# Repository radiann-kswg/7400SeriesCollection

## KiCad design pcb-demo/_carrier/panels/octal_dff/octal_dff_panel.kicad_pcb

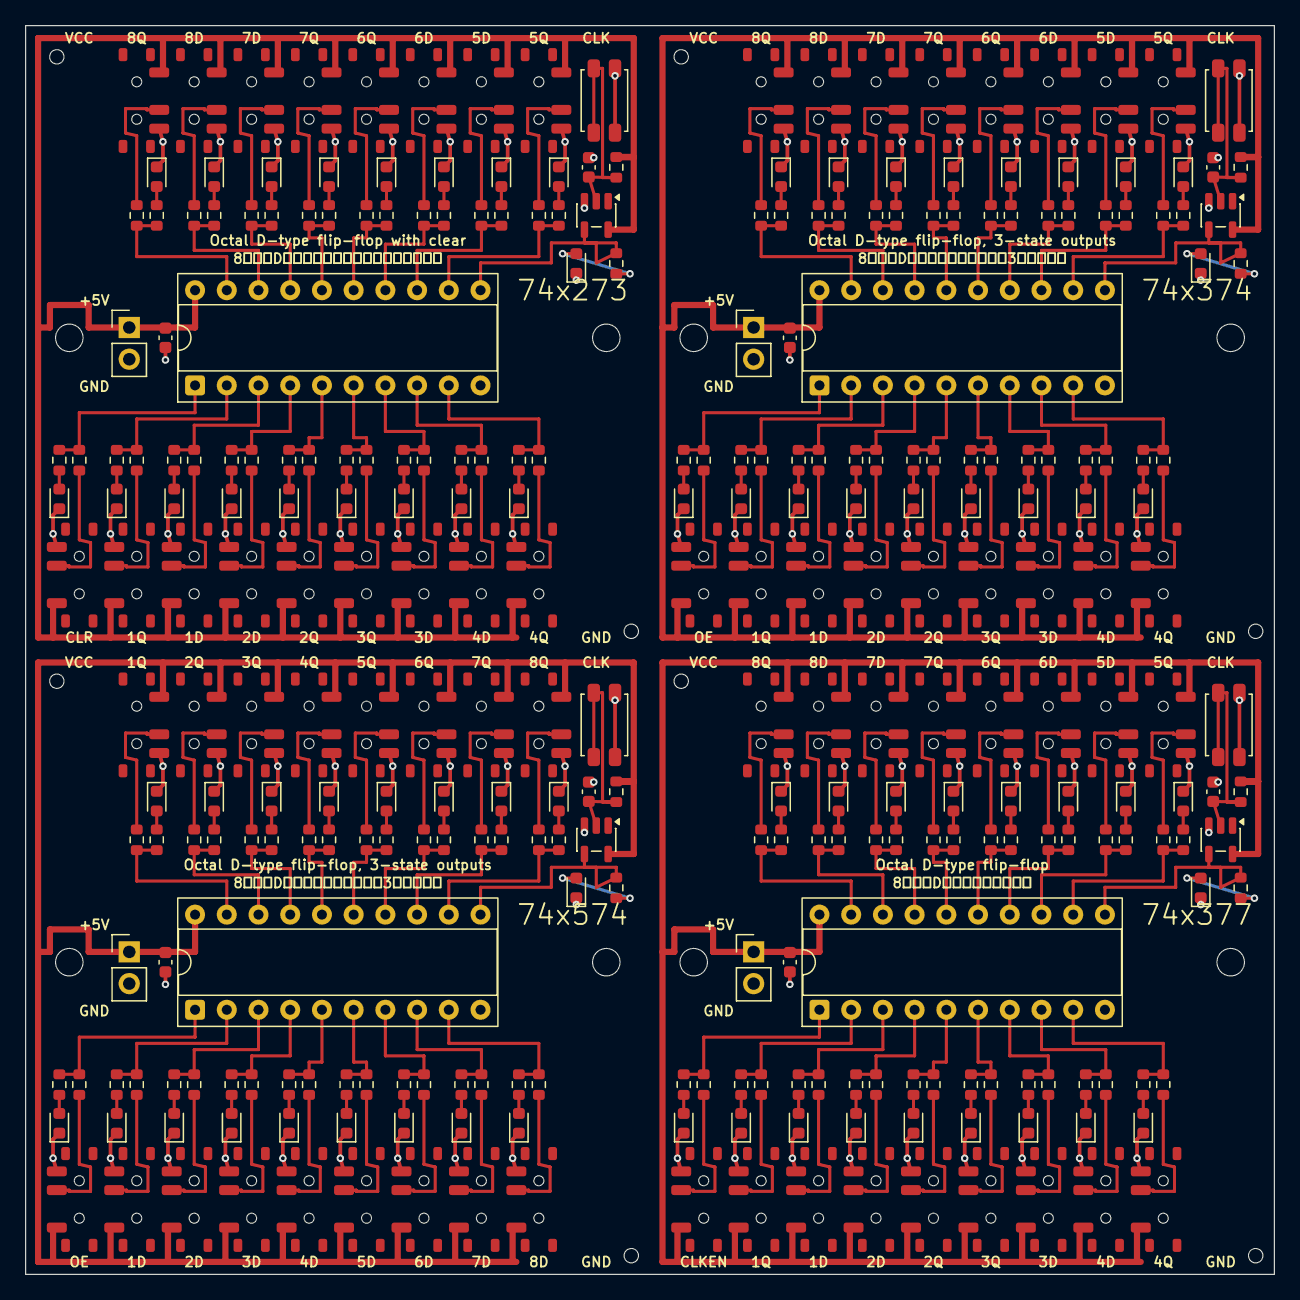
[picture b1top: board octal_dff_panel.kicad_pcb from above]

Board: 2 copper layers, 100.0 x 100.0 mm, 324 parts (0 on the bottom side), 224 nets.

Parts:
A_C1: 100nF; C_0603_1608Metric
A_CK11: 1uF; C_0603_1608Metric
A_D1, A_D3, A_D4, A_D7, A_D8, A_D11, A_D13, A_D14, A_D17, A_D18: RED; LED_0603_1608Metric
A_D2, A_D5, A_D6, A_D9, A_D12, A_D15, A_D16, A_D19: WHITE; LED_0603_1608Metric
A_J1: 5V_IN; PinHeader_1x02_P2.54mm_Vertical
A_MTG1, A_MTG2: MountingHole_2.2mm_M2
A_R1, A_R2, A_R3, A_R4, A_R5, A_R6, A_R7, A_R8, A_R9, A_R11, A_R12, A_R13, A_R14, A_R15, A_R16, A_R17, A_R18, A_R19: 4.7k; R_0603_1608Metric
A_R21, A_R22, A_R23, A_R24, A_R25, A_R26, A_R27, A_R28, A_R29, A_R32, A_R33, A_R34, A_R35, A_R36, A_R37, A_R38, A_R39: 220; R_0603_1608Metric
A_RC11: 10k; R_0603_1608Metric
A_SW1, A_SW2, A_SW3, A_SW4, A_SW5, A_SW6, A_SW7, A_SW8, A_SW9, A_SW12, A_SW13, A_SW14, A_SW15, A_SW16, A_SW17, A_SW18, A_SW19: MSS12C02LS-BB2.0; SW_SPDT_Shouhan_MSS12C02LS
A_SWT11: EVQP2R02M; SW_SPST_EVQP2_ShortPushTravel_H2.1mm
A_TH1, A_TH2: ToolingHole_1.152mm
A_U1: DIP20_Socket_300mil; DIP-20_W7.62mm_Socket
A_UG11: SN74LVC1G14DBVR; SOT-23-5
B_C1: 100nF; C_0603_1608Metric
B_CK11: 1uF; C_0603_1608Metric
B_D1, B_D3, B_D4, B_D7, B_D8, B_D11, B_D13, B_D14, B_D17, B_D18: RED; LED_0603_1608Metric
B_D2, B_D5, B_D6, B_D9, B_D12, B_D15, B_D16, B_D19: WHITE; LED_0603_1608Metric
B_J1: 5V_IN; PinHeader_1x02_P2.54mm_Vertical
B_MTG1, B_MTG2: MountingHole_2.2mm_M2
B_R1, B_R2, B_R3, B_R4, B_R5, B_R6, B_R7, B_R8, B_R9, B_R11, B_R12, B_R13, B_R14, B_R15, B_R16, B_R17, B_R18, B_R19: 4.7k; R_0603_1608Metric
B_R21, B_R22, B_R23, B_R24, B_R25, B_R26, B_R27, B_R28, B_R29, B_R32, B_R33, B_R34, B_R35, B_R36, B_R37, B_R38, B_R39: 220; R_0603_1608Metric
B_RC11: 10k; R_0603_1608Metric
B_SW1, B_SW2, B_SW3, B_SW4, B_SW5, B_SW6, B_SW7, B_SW8, B_SW9, B_SW12, B_SW13, B_SW14, B_SW15, B_SW16, B_SW17, B_SW18, B_SW19: MSS12C02LS-BB2.0; SW_SPDT_Shouhan_MSS12C02LS
B_SWT11: EVQP2R02M; SW_SPST_EVQP2_ShortPushTravel_H2.1mm
B_TH1, B_TH2: ToolingHole_1.152mm
B_U1: DIP20_Socket_300mil; DIP-20_W7.62mm_Socket
B_UG11: SN74LVC1G14DBVR; SOT-23-5
C_C1: 100nF; C_0603_1608Metric
C_CK11: 1uF; C_0603_1608Metric
C_D1, C_D2, C_D3, C_D4, C_D5, C_D6, C_D7, C_D8, C_D9, C_D11: RED; LED_0603_1608Metric
C_D12, C_D13, C_D14, C_D15, C_D16, C_D17, C_D18, C_D19: WHITE; LED_0603_1608Metric
C_J1: 5V_IN; PinHeader_1x02_P2.54mm_Vertical
C_MTG1, C_MTG2: MountingHole_2.2mm_M2
C_R1, C_R2, C_R3, C_R4, C_R5, C_R6, C_R7, C_R8, C_R9, C_R11, C_R12, C_R13, C_R14, C_R15, C_R16, C_R17, C_R18, C_R19: 4.7k; R_0603_1608Metric
C_R21, C_R22, C_R23, C_R24, C_R25, C_R26, C_R27, C_R28, C_R29, C_R32, C_R33, C_R34, C_R35, C_R36, C_R37, C_R38, C_R39: 220; R_0603_1608Metric
C_RC11: 10k; R_0603_1608Metric
C_SW1, C_SW2, C_SW3, C_SW4, C_SW5, C_SW6, C_SW7, C_SW8, C_SW9, C_SW12, C_SW13, C_SW14, C_SW15, C_SW16, C_SW17, C_SW18, C_SW19: MSS12C02LS-BB2.0; SW_SPDT_Shouhan_MSS12C02LS
C_SWT11: EVQP2R02M; SW_SPST_EVQP2_ShortPushTravel_H2.1mm
C_TH1, C_TH2: ToolingHole_1.152mm
C_U1: DIP20_Socket_300mil; DIP-20_W7.62mm_Socket
C_UG11: SN74LVC1G14DBVR; SOT-23-5
D_C1: 100nF; C_0603_1608Metric
D_CK11: 1uF; C_0603_1608Metric
D_D1, D_D3, D_D4, D_D7, D_D8, D_D11, D_D13, D_D14, D_D17, D_D18: RED; LED_0603_1608Metric
D_D2, D_D5, D_D6, D_D9, D_D12, D_D15, D_D16, D_D19: WHITE; LED_0603_1608Metric
D_J1: 5V_IN; PinHeader_1x02_P2.54mm_Vertical
D_MTG1, D_MTG2: MountingHole_2.2mm_M2
D_R1, D_R2, D_R3, D_R4, D_R5, D_R6, D_R7, D_R8, D_R9, D_R11, D_R12, D_R13, D_R14, D_R15, D_R16, D_R17, D_R18, D_R19: 4.7k; R_0603_1608Metric
D_R21, D_R22, D_R23, D_R24, D_R25, D_R26, D_R27, D_R28, D_R29, D_R32, D_R33, D_R34, D_R35, D_R36, D_R37, D_R38, D_R39: 220; R_0603_1608Metric
D_RC11: 10k; R_0603_1608Metric
D_SW1, D_SW2, D_SW3, D_SW4, D_SW5, D_SW6, D_SW7, D_SW8, D_SW9, D_SW12, D_SW13, D_SW14, D_SW15, D_SW16, D_SW17, D_SW18, D_SW19: MSS12C02LS-BB2.0; SW_SPDT_Shouhan_MSS12C02LS
D_SWT11: EVQP2R02M; SW_SPST_EVQP2_ShortPushTravel_H2.1mm
D_TH1, D_TH2: ToolingHole_1.152mm
D_U1: DIP20_Socket_300mil; DIP-20_W7.62mm_Socket
D_UG11: SN74LVC1G14DBVR; SOT-23-5

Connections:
A_+5V: A_C1.1, A_J1.1, A_RC11.1, A_SW1.1, A_SW2.1, A_SW3.1, A_SW4.1, A_SW5.1, A_SW6.1, A_SW7.1, A_SW8.1, A_SW9.1, A_SW12.1, A_SW13.1, A_SW14.1, A_SW15.1, A_SW16.1, A_SW17.1, A_SW18.1, A_SW19.1, A_U1.20, A_UG11.5
A_/CLKR11: A_CK11.1, A_RC11.2, A_SWT11.2, A_UG11.2
A_/LA1: A_D1.2, A_R1.1
A_/LA2: A_D2.2, A_R2.1
A_/LA3: A_D3.2, A_R3.1
A_/LA4: A_D4.2, A_R4.1
A_/LA5: A_D5.2, A_R5.1
A_/LA6: A_D6.2, A_R6.1
A_/LA7: A_D7.2, A_R7.1
A_/LA8: A_D8.2, A_R8.1
A_/LA9: A_D9.2, A_R9.1
A_/LA11: A_D11.2, A_R11.2
A_/LA12: A_D12.2, A_R12.1
A_/LA13: A_D13.2, A_R13.1
A_/LA14: A_D14.2, A_R14.1
A_/LA15: A_D15.2, A_R15.1
A_/LA16: A_D16.2, A_R16.1
A_/LA17: A_D17.2, A_R17.1
A_/LA18: A_D18.2, A_R18.1
A_/LA19: A_D19.2, A_R19.1
A_/P1: A_R1.2, A_R21.2, A_U1.1
A_/P2: A_R2.2, A_R22.2, A_U1.2
A_/P3: A_R3.2, A_R23.2, A_U1.3
A_/P4: A_R4.2, A_R24.2, A_U1.4
A_/P5: A_R5.2, A_R25.2, A_U1.5
A_/P6: A_R6.2, A_R26.2, A_U1.6
A_/P7: A_R7.2, A_R27.2, A_U1.7
A_/P8: A_R8.2, A_R28.2, A_U1.8
A_/P9: A_R9.2, A_R29.2, A_U1.9
A_/P11: A_R11.1, A_U1.11, A_UG11.4
A_/P12: A_R12.2, A_R32.2, A_U1.12
A_/P13: A_R13.2, A_R33.2, A_U1.13
A_/P14: A_R14.2, A_R34.2, A_U1.14
A_/P15: A_R15.2, A_R35.2, A_U1.15
A_/P16: A_R16.2, A_R36.2, A_U1.16
A_/P17: A_R17.2, A_R37.2, A_U1.17
A_/P18: A_R18.2, A_R38.2, A_U1.18
A_/P19: A_R19.2, A_R39.2, A_U1.19
A_/SWC1: A_R21.1, A_SW1.2
A_/SWC2: A_R22.1, A_SW2.2
A_/SWC3: A_R23.1, A_SW3.2
A_/SWC4: A_R24.1, A_SW4.2
A_/SWC5: A_R25.1, A_SW5.2
A_/SWC6: A_R26.1, A_SW6.2
A_/SWC7: A_R27.1, A_SW7.2
A_/SWC8: A_R28.1, A_SW8.2
A_/SWC9: A_R29.1, A_SW9.2
A_/SWC12: A_R32.1, A_SW12.2
A_/SWC13: A_R33.1, A_SW13.2
A_/SWC14: A_R34.1, A_SW14.2
A_/SWC15: A_R35.1, A_SW15.2
A_/SWC16: A_R36.1, A_SW16.2
A_/SWC17: A_R37.1, A_SW17.2
A_/SWC18: A_R38.1, A_SW18.2
A_/SWC19: A_R39.1, A_SW19.2
A_GND: A_C1.2, A_CK11.2, A_D1.1, A_D2.1, A_D3.1, A_D4.1, A_D5.1, A_D6.1, A_D7.1, A_D8.1, A_D9.1, A_D11.1, A_D12.1, A_D13.1, A_D14.1, A_D15.1, A_D16.1, A_D17.1, A_D18.1, A_D19.1, A_J1.2, A_SW1.3, A_SW2.3, A_SW3.3, A_SW4.3, A_SW5.3, A_SW6.3, A_SW7.3, A_SW8.3, A_SW9.3, A_SW12.3, A_SW13.3, A_SW14.3, A_SW15.3, A_SW16.3, A_SW17.3, A_SW18.3, A_SW19.3, A_SWT11.1, A_U1.10, A_UG11.3
B_+5V: B_C1.1, B_J1.1, B_RC11.1, B_SW1.1, B_SW2.1, B_SW3.1, B_SW4.1, B_SW5.1, B_SW6.1, B_SW7.1, B_SW8.1, B_SW9.1, B_SW12.1, B_SW13.1, B_SW14.1, B_SW15.1, B_SW16.1, B_SW17.1, B_SW18.1, B_SW19.1, B_U1.20, B_UG11.5
B_/CLKR11: B_CK11.1, B_RC11.2, B_SWT11.2, B_UG11.2
B_/LA1: B_D1.2, B_R1.1
B_/LA2: B_D2.2, B_R2.1
B_/LA3: B_D3.2, B_R3.1
B_/LA4: B_D4.2, B_R4.1
B_/LA5: B_D5.2, B_R5.1
B_/LA6: B_D6.2, B_R6.1
B_/LA7: B_D7.2, B_R7.1
B_/LA8: B_D8.2, B_R8.1
B_/LA9: B_D9.2, B_R9.1
B_/LA11: B_D11.2, B_R11.2
B_/LA12: B_D12.2, B_R12.1
B_/LA13: B_D13.2, B_R13.1
B_/LA14: B_D14.2, B_R14.1
B_/LA15: B_D15.2, B_R15.1
B_/LA16: B_D16.2, B_R16.1
B_/LA17: B_D17.2, B_R17.1
B_/LA18: B_D18.2, B_R18.1
B_/LA19: B_D19.2, B_R19.1
B_/P1: B_R1.2, B_R21.2, B_U1.1
B_/P2: B_R2.2, B_R22.2, B_U1.2
B_/P3: B_R3.2, B_R23.2, B_U1.3
B_/P4: B_R4.2, B_R24.2, B_U1.4
B_/P5: B_R5.2, B_R25.2, B_U1.5
B_/P6: B_R6.2, B_R26.2, B_U1.6
B_/P7: B_R7.2, B_R27.2, B_U1.7
B_/P8: B_R8.2, B_R28.2, B_U1.8
B_/P9: B_R9.2, B_R29.2, B_U1.9
B_/P11: B_R11.1, B_U1.11, B_UG11.4
B_/P12: B_R12.2, B_R32.2, B_U1.12
B_/P13: B_R13.2, B_R33.2, B_U1.13
B_/P14: B_R14.2, B_R34.2, B_U1.14
B_/P15: B_R15.2, B_R35.2, B_U1.15
B_/P16: B_R16.2, B_R36.2, B_U1.16
B_/P17: B_R17.2, B_R37.2, B_U1.17
B_/P18: B_R18.2, B_R38.2, B_U1.18
B_/P19: B_R19.2, B_R39.2, B_U1.19
B_/SWC1: B_R21.1, B_SW1.2
B_/SWC2: B_R22.1, B_SW2.2
B_/SWC3: B_R23.1, B_SW3.2
B_/SWC4: B_R24.1, B_SW4.2
B_/SWC5: B_R25.1, B_SW5.2
B_/SWC6: B_R26.1, B_SW6.2
B_/SWC7: B_R27.1, B_SW7.2
B_/SWC8: B_R28.1, B_SW8.2
B_/SWC9: B_R29.1, B_SW9.2
B_/SWC12: B_R32.1, B_SW12.2
B_/SWC13: B_R33.1, B_SW13.2
B_/SWC14: B_R34.1, B_SW14.2
B_/SWC15: B_R35.1, B_SW15.2
B_/SWC16: B_R36.1, B_SW16.2
B_/SWC17: B_R37.1, B_SW17.2
B_/SWC18: B_R38.1, B_SW18.2
B_/SWC19: B_R39.1, B_SW19.2
B_GND: B_C1.2, B_CK11.2, B_D1.1, B_D2.1, B_D3.1, B_D4.1, B_D5.1, B_D6.1, B_D7.1, B_D8.1, B_D9.1, B_D11.1, B_D12.1, B_D13.1, B_D14.1, B_D15.1, B_D16.1, B_D17.1, B_D18.1, B_D19.1, B_J1.2, B_SW1.3, B_SW2.3, B_SW3.3, B_SW4.3, B_SW5.3, B_SW6.3, B_SW7.3, B_SW8.3, B_SW9.3, B_SW12.3, B_SW13.3, B_SW14.3, B_SW15.3, B_SW16.3, B_SW17.3, B_SW18.3, B_SW19.3, B_SWT11.1, B_U1.10, B_UG11.3
C_+5V: C_C1.1, C_J1.1, C_RC11.1, C_SW1.1, C_SW2.1, C_SW3.1, C_SW4.1, C_SW5.1, C_SW6.1, C_SW7.1, C_SW8.1, C_SW9.1, C_SW12.1, C_SW13.1, C_SW14.1, C_SW15.1, C_SW16.1, C_SW17.1, C_SW18.1, C_SW19.1, C_U1.20, C_UG11.5
C_/CLKR11: C_CK11.1, C_RC11.2, C_SWT11.2, C_UG11.2
C_/LA1: C_D1.2, C_R1.1
C_/LA2: C_D2.2, C_R2.1
C_/LA3: C_D3.2, C_R3.1
C_/LA4: C_D4.2, C_R4.1
C_/LA5: C_D5.2, C_R5.1
C_/LA6: C_D6.2, C_R6.1
C_/LA7: C_D7.2, C_R7.1
C_/LA8: C_D8.2, C_R8.1
C_/LA9: C_D9.2, C_R9.1
C_/LA11: C_D11.2, C_R11.2
C_/LA12: C_D12.2, C_R12.1
C_/LA13: C_D13.2, C_R13.1
C_/LA14: C_D14.2, C_R14.1
C_/LA15: C_D15.2, C_R15.1
C_/LA16: C_D16.2, C_R16.1
C_/LA17: C_D17.2, C_R17.1
C_/LA18: C_D18.2, C_R18.1
C_/LA19: C_D19.2, C_R19.1
C_/P1: C_R1.2, C_R21.2, C_U1.1
C_/P2: C_R2.2, C_R22.2, C_U1.2
C_/P3: C_R3.2, C_R23.2, C_U1.3
C_/P4: C_R4.2, C_R24.2, C_U1.4
C_/P5: C_R5.2, C_R25.2, C_U1.5
C_/P6: C_R6.2, C_R26.2, C_U1.6
C_/P7: C_R7.2, C_R27.2, C_U1.7
C_/P8: C_R8.2, C_R28.2, C_U1.8
C_/P9: C_R9.2, C_R29.2, C_U1.9
C_/P11: C_R11.1, C_U1.11, C_UG11.4
C_/P12: C_R12.2, C_R32.2, C_U1.12
C_/P13: C_R13.2, C_R33.2, C_U1.13
C_/P14: C_R14.2, C_R34.2, C_U1.14
C_/P15: C_R15.2, C_R35.2, C_U1.15
C_/P16: C_R16.2, C_R36.2, C_U1.16
C_/P17: C_R17.2, C_R37.2, C_U1.17
C_/P18: C_R18.2, C_R38.2, C_U1.18
C_/P19: C_R19.2, C_R39.2, C_U1.19
C_/SWC1: C_R21.1, C_SW1.2
C_/SWC2: C_R22.1, C_SW2.2
C_/SWC3: C_R23.1, C_SW3.2
C_/SWC4: C_R24.1, C_SW4.2
C_/SWC5: C_R25.1, C_SW5.2
C_/SWC6: C_R26.1, C_SW6.2
C_/SWC7: C_R27.1, C_SW7.2
C_/SWC8: C_R28.1, C_SW8.2
C_/SWC9: C_R29.1, C_SW9.2
C_/SWC12: C_R32.1, C_SW12.2
C_/SWC13: C_R33.1, C_SW13.2
C_/SWC14: C_R34.1, C_SW14.2
C_/SWC15: C_R35.1, C_SW15.2
C_/SWC16: C_R36.1, C_SW16.2
C_/SWC17: C_R37.1, C_SW17.2
C_/SWC18: C_R38.1, C_SW18.2
C_/SWC19: C_R39.1, C_SW19.2
C_GND: C_C1.2, C_CK11.2, C_D1.1, C_D2.1, C_D3.1, C_D4.1, C_D5.1, C_D6.1, C_D7.1, C_D8.1, C_D9.1, C_D11.1, C_D12.1, C_D13.1, C_D14.1, C_D15.1, C_D16.1, C_D17.1, C_D18.1, C_D19.1, C_J1.2, C_SW1.3, C_SW2.3, C_SW3.3, C_SW4.3, C_SW5.3, C_SW6.3, C_SW7.3, C_SW8.3, C_SW9.3, C_SW12.3, C_SW13.3, C_SW14.3, C_SW15.3, C_SW16.3, C_SW17.3, C_SW18.3, C_SW19.3, C_SWT11.1, C_U1.10, C_UG11.3
D_+5V: D_C1.1, D_J1.1, D_RC11.1, D_SW1.1, D_SW2.1, D_SW3.1, D_SW4.1, D_SW5.1, D_SW6.1, D_SW7.1, D_SW8.1, D_SW9.1, D_SW12.1, D_SW13.1, D_SW14.1, D_SW15.1, D_SW16.1, D_SW17.1, D_SW18.1, D_SW19.1, D_U1.20, D_UG11.5
D_/CLKR11: D_CK11.1, D_RC11.2, D_SWT11.2, D_UG11.2
D_/LA1: D_D1.2, D_R1.1
D_/LA2: D_D2.2, D_R2.1
D_/LA3: D_D3.2, D_R3.1
D_/LA4: D_D4.2, D_R4.1
D_/LA5: D_D5.2, D_R5.1
D_/LA6: D_D6.2, D_R6.1
D_/LA7: D_D7.2, D_R7.1
D_/LA8: D_D8.2, D_R8.1
D_/LA9: D_D9.2, D_R9.1
D_/LA11: D_D11.2, D_R11.2
D_/LA12: D_D12.2, D_R12.1
D_/LA13: D_D13.2, D_R13.1
D_/LA14: D_D14.2, D_R14.1
D_/LA15: D_D15.2, D_R15.1
D_/LA16: D_D16.2, D_R16.1
D_/LA17: D_D17.2, D_R17.1
D_/LA18: D_D18.2, D_R18.1
D_/LA19: D_D19.2, D_R19.1
D_/P1: D_R1.2, D_R21.2, D_U1.1
D_/P2: D_R2.2, D_R22.2, D_U1.2
D_/P3: D_R3.2, D_R23.2, D_U1.3
D_/P4: D_R4.2, D_R24.2, D_U1.4
D_/P5: D_R5.2, D_R25.2, D_U1.5
D_/P6: D_R6.2, D_R26.2, D_U1.6
D_/P7: D_R7.2, D_R27.2, D_U1.7
D_/P8: D_R8.2, D_R28.2, D_U1.8
D_/P9: D_R9.2, D_R29.2, D_U1.9
D_/P11: D_R11.1, D_U1.11, D_UG11.4
D_/P12: D_R12.2, D_R32.2, D_U1.12
D_/P13: D_R13.2, D_R33.2, D_U1.13
D_/P14: D_R14.2, D_R34.2, D_U1.14
D_/P15: D_R15.2, D_R35.2, D_U1.15
D_/P16: D_R16.2, D_R36.2, D_U1.16
D_/P17: D_R17.2, D_R37.2, D_U1.17
D_/P18: D_R18.2, D_R38.2, D_U1.18
D_/P19: D_R19.2, D_R39.2, D_U1.19
D_/SWC1: D_R21.1, D_SW1.2
D_/SWC2: D_R22.1, D_SW2.2
D_/SWC3: D_R23.1, D_SW3.2
D_/SWC4: D_R24.1, D_SW4.2
D_/SWC5: D_R25.1, D_SW5.2
D_/SWC6: D_R26.1, D_SW6.2
D_/SWC7: D_R27.1, D_SW7.2
D_/SWC8: D_R28.1, D_SW8.2
D_/SWC9: D_R29.1, D_SW9.2
D_/SWC12: D_R32.1, D_SW12.2
D_/SWC13: D_R33.1, D_SW13.2
D_/SWC14: D_R34.1, D_SW14.2
D_/SWC15: D_R35.1, D_SW15.2
D_/SWC16: D_R36.1, D_SW16.2
D_/SWC17: D_R37.1, D_SW17.2
D_/SWC18: D_R38.1, D_SW18.2
D_/SWC19: D_R39.1, D_SW19.2
D_GND: D_C1.2, D_CK11.2, D_D1.1, D_D2.1, D_D3.1, D_D4.1, D_D5.1, D_D6.1, D_D7.1, D_D8.1, D_D9.1, D_D11.1, D_D12.1, D_D13.1, D_D14.1, D_D15.1, D_D16.1, D_D17.1, D_D18.1, D_D19.1, D_J1.2, D_SW1.3, D_SW2.3, D_SW3.3, D_SW4.3, D_SW5.3, D_SW6.3, D_SW7.3, D_SW8.3, D_SW9.3, D_SW12.3, D_SW13.3, D_SW14.3, D_SW15.3, D_SW16.3, D_SW17.3, D_SW18.3, D_SW19.3, D_SWT11.1, D_U1.10, D_UG11.3

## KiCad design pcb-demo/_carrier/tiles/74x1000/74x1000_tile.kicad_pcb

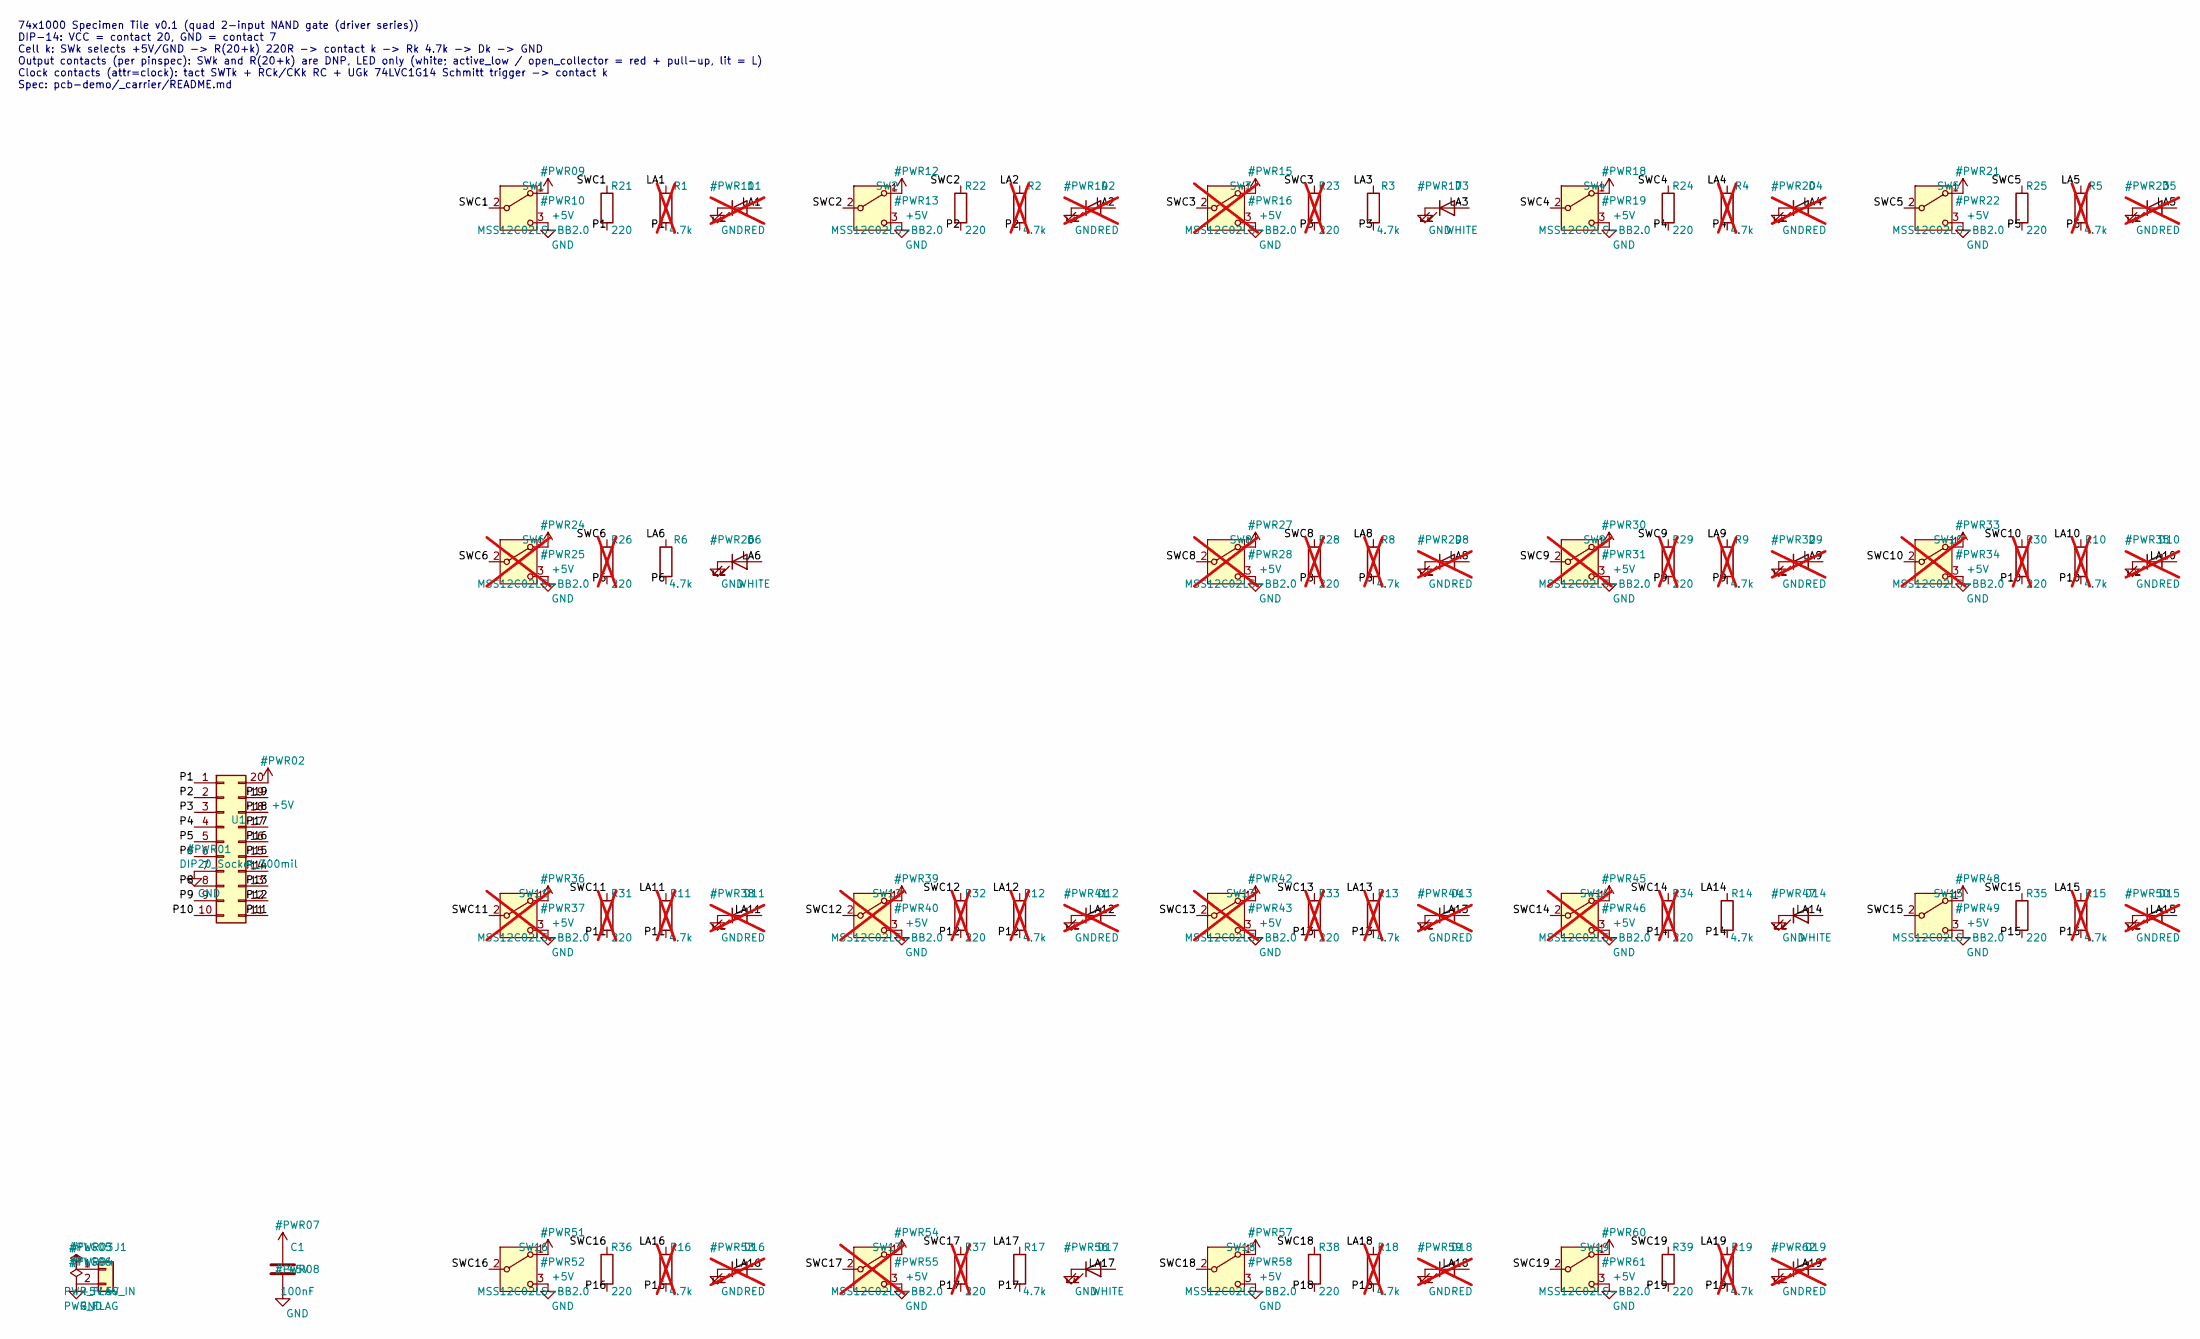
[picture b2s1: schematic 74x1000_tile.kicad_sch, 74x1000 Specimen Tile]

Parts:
C1: 100nF; C_0603_1608Metric; MPN CC0603KRX7R9BB104; LCSC Part # C14663
D1, D2, D4, D5, D8, D9, D10, D11, D12, D13, D15, D16, D18, D19: RED; LED_0603_1608Metric; MPN KT-0603R; LCSC Part # C2286; not fitted
D3, D6, D14, D17: WHITE; LED_0603_1608Metric; MPN KT-0603W; LCSC Part # C2290
J1: 5V_IN; PinHeader_1x02_P2.54mm_Vertical
R1, R2, R4, R5, R8, R9, R10, R11, R12, R13, R15, R16, R18, R19: 4.7k; R_0603_1608Metric; MPN 0603WAF4701T5E; LCSC Part # C23162; not fitted
R3, R6, R14, R17: 4.7k; R_0603_1608Metric; MPN 0603WAF4701T5E; LCSC Part # C23162
R21, R22, R24, R25, R35, R36, R38, R39: 220; R_0603_1608Metric; MPN 0603WAF2200T5E; LCSC Part # C22962
R23, R26, R28, R29, R30, R31, R32, R33, R34, R37: 220; R_0603_1608Metric; MPN 0603WAF2200T5E; LCSC Part # C22962; not fitted
SW1, SW2, SW4, SW5, SW15, SW16, SW18, SW19: MSS12C02LS-BB2.0; SW_SPDT_Shouhan_MSS12C02LS; MPN MSS12C02LS-BB2.0; LCSC Part # C3008585
SW3, SW6, SW8, SW9, SW10, SW11, SW12, SW13, SW14, SW17: MSS12C02LS-BB2.0; SW_SPDT_Shouhan_MSS12C02LS; MPN MSS12C02LS-BB2.0; LCSC Part # C3008585; not fitted
U1: DIP20_Socket_300mil; DIP-20_W7.62mm_Socket

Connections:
+5V: C1.1, J1.1, SW1.1 (A), SW2.1 (A), SW3.1 (A), SW4.1 (A), SW5.1 (A), SW6.1 (A), SW8.1 (A), SW9.1 (A), SW10.1 (A), SW11.1 (A), SW12.1 (A), SW13.1 (A), SW14.1 (A), SW15.1 (A), SW16.1 (A), SW17.1 (A), SW18.1 (A), SW19.1 (A), U1.20
/LA1: D1.2 (A), R1.1
/LA2: D2.2 (A), R2.1
/LA3: D3.2 (A), R3.1
/LA4: D4.2 (A), R4.1
/LA5: D5.2 (A), R5.1
/LA6: D6.2 (A), R6.1
/LA8: D8.2 (A), R8.1
/LA9: D9.2 (A), R9.1
/LA10: D10.2 (A), R10.1
/LA11: D11.2 (A), R11.1
/LA12: D12.2 (A), R12.1
/LA13: D13.2 (A), R13.1
/LA14: D14.2 (A), R14.1
/LA15: D15.2 (A), R15.1
/LA16: D16.2 (A), R16.1
/LA17: D17.2 (A), R17.1
/LA18: D18.2 (A), R18.1
/LA19: D19.2 (A), R19.1
/P1: R1.2, R21.2, U1.1
/P2: R2.2, R22.2, U1.2
/P3: R3.2, R23.2, U1.3
/P4: R4.2, R24.2, U1.4
/P5: R5.2, R25.2, U1.5
/P6: R6.2, R26.2, U1.6
/P8: R8.2, R28.2, U1.8
/P9: R9.2, R29.2, U1.9
/P10: R10.2, R30.2, U1.10
/P11: R11.2, R31.2, U1.11
/P12: R12.2, R32.2, U1.12
/P13: R13.2, R33.2, U1.13
/P14: R14.2, R34.2, U1.14
/P15: R15.2, R35.2, U1.15
/P16: R16.2, R36.2, U1.16
/P17: R17.2, R37.2, U1.17
/P18: R18.2, R38.2, U1.18
/P19: R19.2, R39.2, U1.19
/SWC1: R21.1, SW1.2 (B)
/SWC2: R22.1, SW2.2 (B)
/SWC3: R23.1, SW3.2 (B)
/SWC4: R24.1, SW4.2 (B)
/SWC5: R25.1, SW5.2 (B)
/SWC6: R26.1, SW6.2 (B)
/SWC8: R28.1, SW8.2 (B)
/SWC9: R29.1, SW9.2 (B)
/SWC10: R30.1, SW10.2 (B)
/SWC11: R31.1, SW11.2 (B)
/SWC12: R32.1, SW12.2 (B)
/SWC13: R33.1, SW13.2 (B)
/SWC14: R34.1, SW14.2 (B)
/SWC15: R35.1, SW15.2 (B)
/SWC16: R36.1, SW16.2 (B)
/SWC17: R37.1, SW17.2 (B)
/SWC18: R38.1, SW18.2 (B)
/SWC19: R39.1, SW19.2 (B)
GND: C1.2, D1.1 (K), D2.1 (K), D3.1 (K), D4.1 (K), D5.1 (K), D6.1 (K), D8.1 (K), D9.1 (K), D10.1 (K), D11.1 (K), D12.1 (K), D13.1 (K), D14.1 (K), D15.1 (K), D16.1 (K), D17.1 (K), D18.1 (K), D19.1 (K), J1.2, SW1.3 (C), SW2.3 (C), SW3.3 (C), SW4.3 (C), SW5.3 (C), SW6.3 (C), SW8.3 (C), SW9.3 (C), SW10.3 (C), SW11.3 (C), SW12.3 (C), SW13.3 (C), SW14.3 (C), SW15.3 (C), SW16.3 (C), SW17.3 (C), SW18.3 (C), SW19.3 (C), U1.7

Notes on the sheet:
74x1000 Specimen Tile v0.1 (quad 2-input NAND gate (driver series)) DIP-14: VCC = contact 20, GND = contact 7 Cell k: SWk selects +5V/GND -> R(20+k) 220R -> contact k -> Rk 4.7k -> Dk -> GND Output contacts (per pinspec): SWk and R(20+k) are DNP, LED only (white; active_low / open_collector = red +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

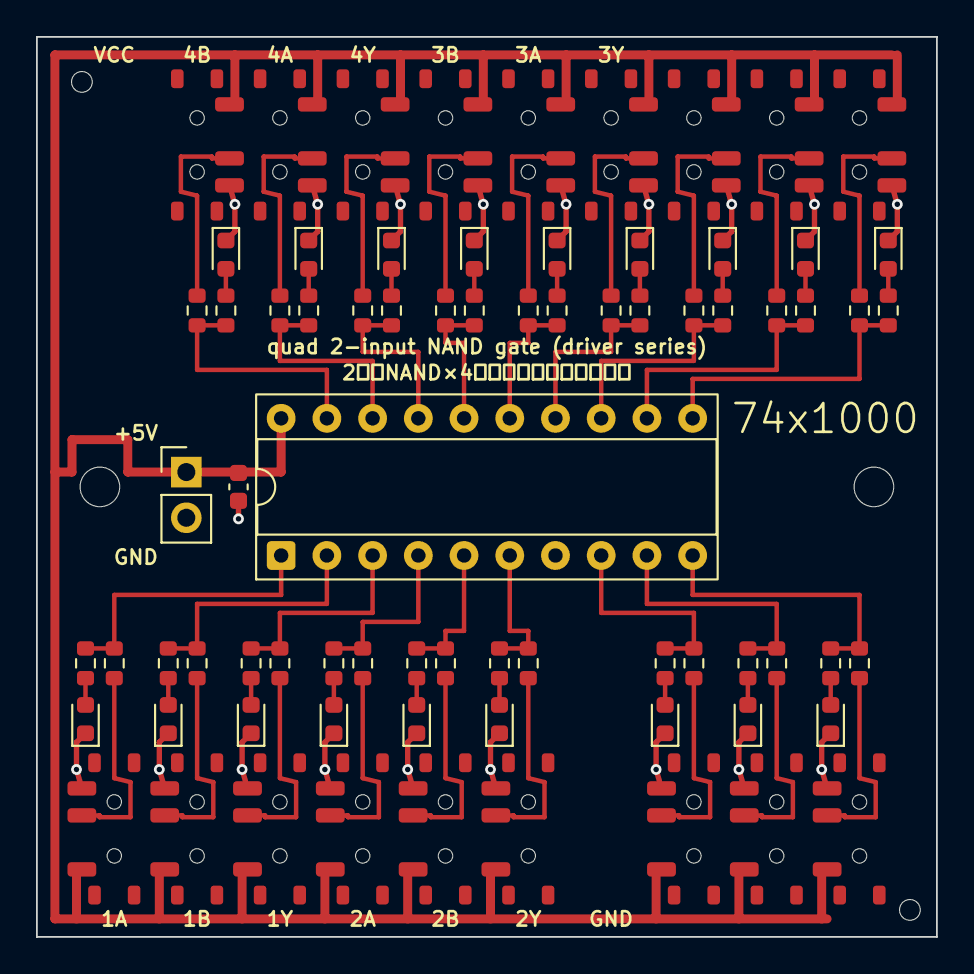
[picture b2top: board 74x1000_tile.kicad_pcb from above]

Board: 2 copper layers, 50.0 x 50.0 mm, 79 parts (0 on the bottom side), 56 nets.

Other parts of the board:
MTG1, MTG2: MountingHole_2.2mm_M2
TH1, TH2: ToolingHole_1.152mm

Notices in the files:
pcb-demo/_carrier/panels/octal_dff/octal_dff_panel.kicad_pcb:
MIT License
